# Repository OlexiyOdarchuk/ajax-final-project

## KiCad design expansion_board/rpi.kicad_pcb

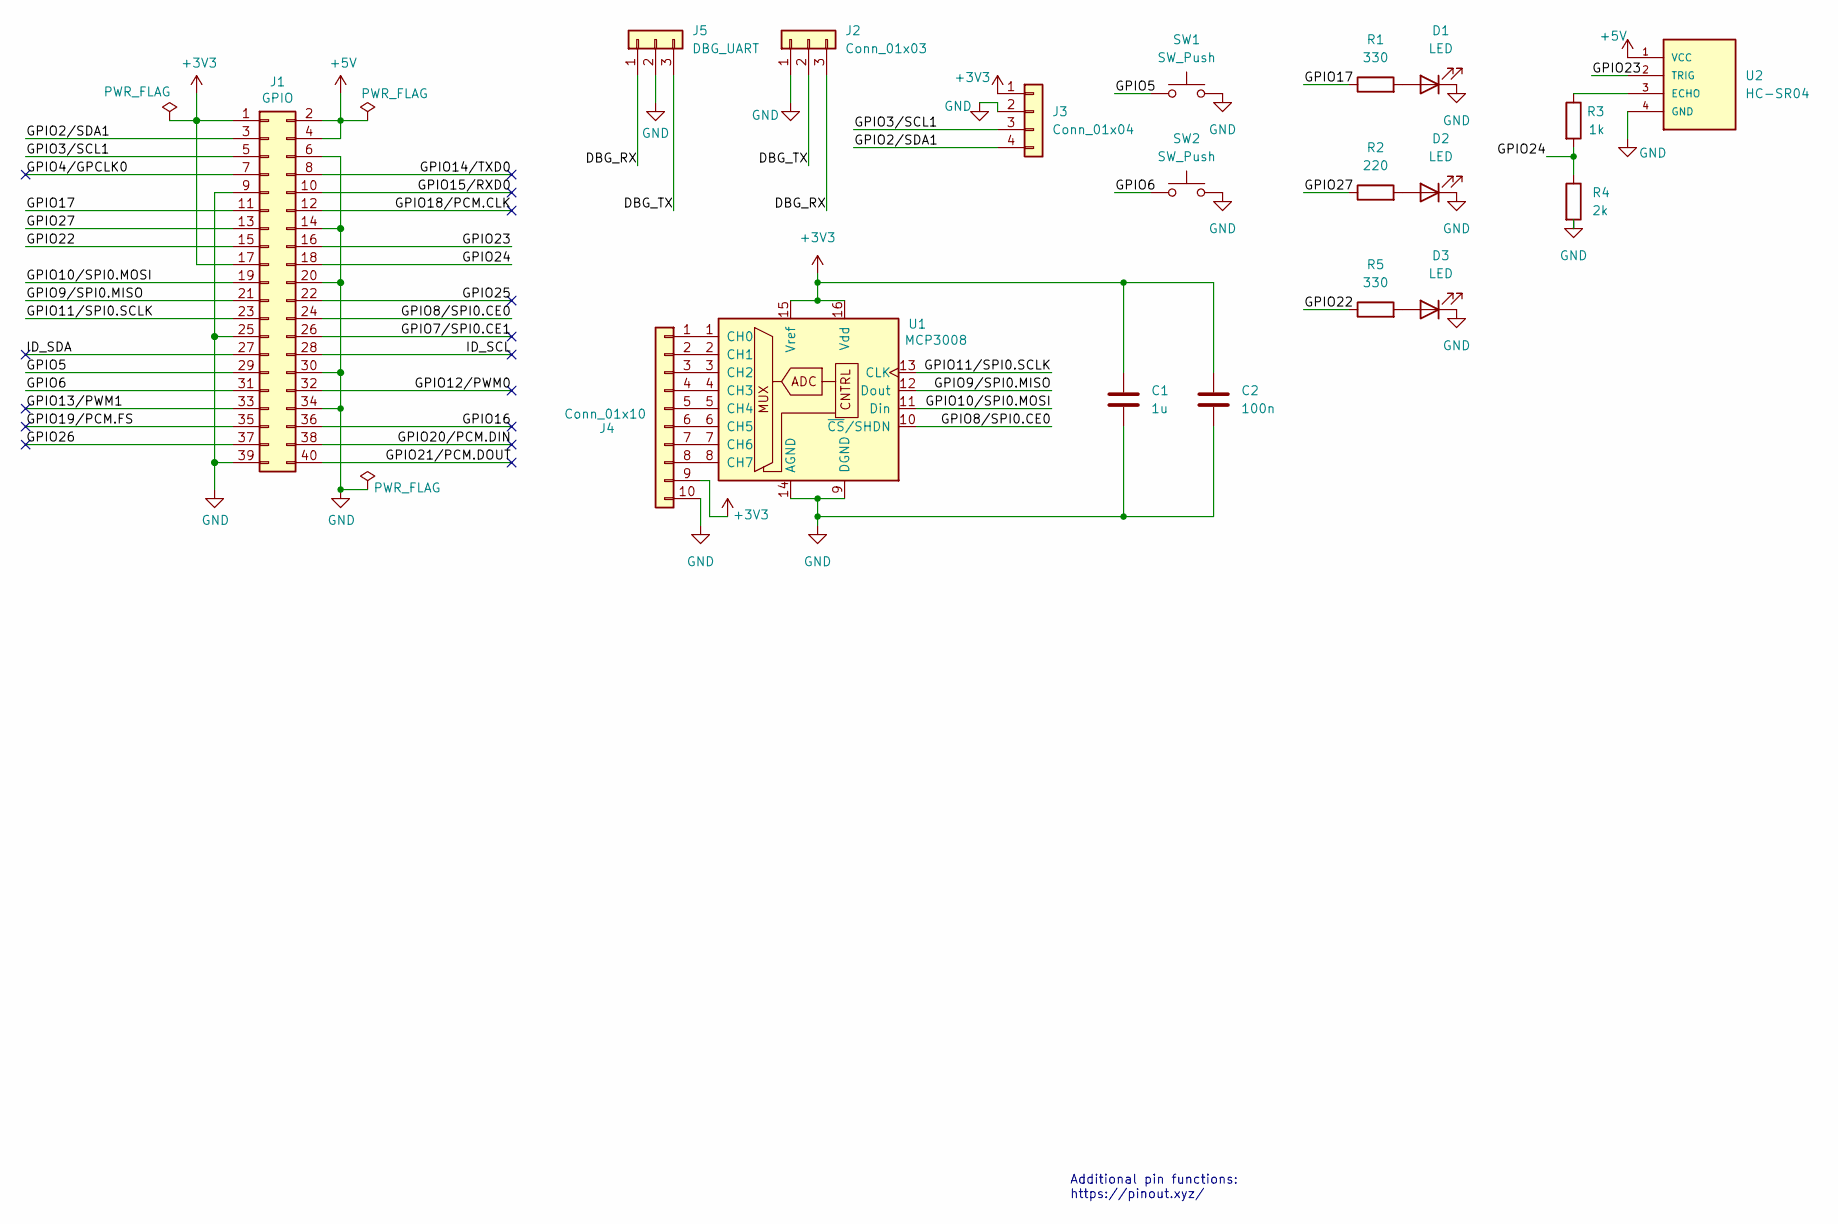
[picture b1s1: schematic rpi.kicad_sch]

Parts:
C1: 1u; C_Disc_D5.0mm_W2.5mm_P5.00mm
C2: 100n; C_Disc_D5.0mm_W2.5mm_P5.00mm
D1, D2, D3: LED; LED_D5.0mm
J1: GPIO; PinSocket_2x20_P2.54mm_Vertical
J2: Conn_01x03; PinHeader_1x03_P2.54mm_Horizontal
J3: Conn_01x04; PinSocket_1x04_P2.54mm_Vertical
J4: Conn_01x10; PinHeader_1x10_P2.54mm_Vertical
J5: DBG_UART; PinHeader_1x03_P2.54mm_Vertical
R1, R5: 330; R_Axial_DIN0207_L6.3mm_D2.5mm_P10.16mm_Horizontal
R2: 220; R_Axial_DIN0207_L6.3mm_D2.5mm_P10.16mm_Horizontal
R3: 1k; R_Axial_DIN0207_L6.3mm_D2.5mm_P10.16mm_Horizontal
R4: 2k; R_Axial_DIN0207_L6.3mm_D2.5mm_P10.16mm_Horizontal
SW1, SW2: SW_Push; SW_PUSH_6mm
U1: MCP3008; DIP-16_W7.62mm
U2: HC-SR04; XCVR_HC-SR04

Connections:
+3V3: C1.1, C2.1, J1.1, J1.17, J3.1, J4.9, U1.15 (Vref), U1.16 (Vdd)
+5V: J1.2, J1.4, U2.1 (VCC)
/DBG_RX: J2.3, J5.1
/DBG_TX: J2.2, J5.3
/GPIO2/SDA1: J1.3, J3.4
/GPIO3/SCL1: J1.5, J3.3
/GPIO4/GPCLK0: J1.7
/GPIO5: J1.29, SW1.1
/GPIO6: J1.31, SW2.1
/GPIO7/SPI0.CE1: J1.26
/GPIO8/SPI0.CE0: J1.24, U1.10 (~CS/SHDN)
/GPIO9/SPI0.MISO: J1.21, U1.12 (Dout)
/GPIO10/SPI0.MOSI: J1.19, U1.11 (Din)
/GPIO11/SPI0.SCLK: J1.23, U1.13 (CLK)
/GPIO12/PWM0: J1.32
/GPIO13/PWM1: J1.33
/GPIO14/TXD0: J1.8
/GPIO15/RXD0: J1.10
/GPIO16: J1.36
/GPIO17: J1.11, R1.1
/GPIO18/PCM.CLK: J1.12
/GPIO19/PCM.FS: J1.35
/GPIO20/PCM.DIN: J1.38
/GPIO21/PCM.DOUT: J1.40
/GPIO22: J1.15, R5.1
/GPIO23: J1.16, U2.2 (TRIG)
/GPIO24: J1.18, R3.2, R4.1
/GPIO25: J1.22
/GPIO26: J1.37
/GPIO27: J1.13, R2.1
/ID_SCL: J1.28
/ID_SDA: J1.27
GND: C1.2, C2.2, D1.1 (K), D2.1 (K), D3.1 (K), J1.6, J1.9, J1.14, J1.20, J1.25, J1.30, J1.34, J1.39, J2.1, J3.2, J4.10, J5.2, R4.2, SW1.2, SW2.2, U1.9 (DGND), U1.14 (AGND), U2.4 (GND)
unnamed: D1.2 (A), R1.2
unnamed: D2.2 (A), R2.2
unnamed: D3.2 (A), R5.2
unnamed: J4.1, U1.1 (CH0)
unnamed: J4.2, U1.2 (CH1)
unnamed: J4.3, U1.3 (CH2)
unnamed: J4.4, U1.4 (CH3)
unnamed: J4.5, U1.5 (CH4)
unnamed: J4.6, U1.6 (CH5)
unnamed: J4.7, U1.7 (CH6)
unnamed: J4.8, U1.8 (CH7)
unnamed: R3.1, U2.3 (ECHO)

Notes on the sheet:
Additional pin functions: https://pinout.xyz/

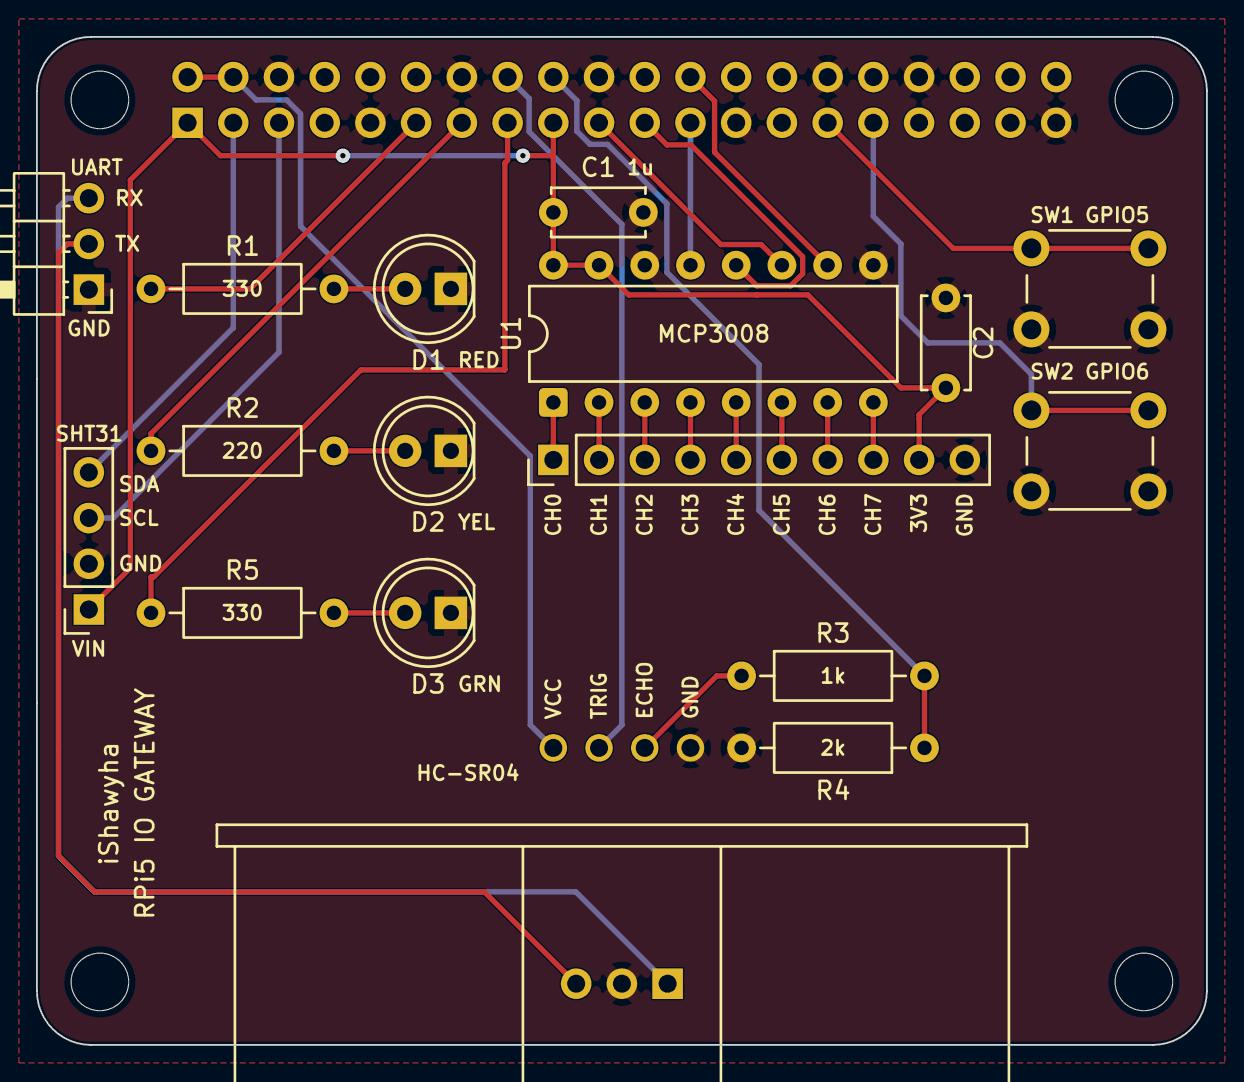
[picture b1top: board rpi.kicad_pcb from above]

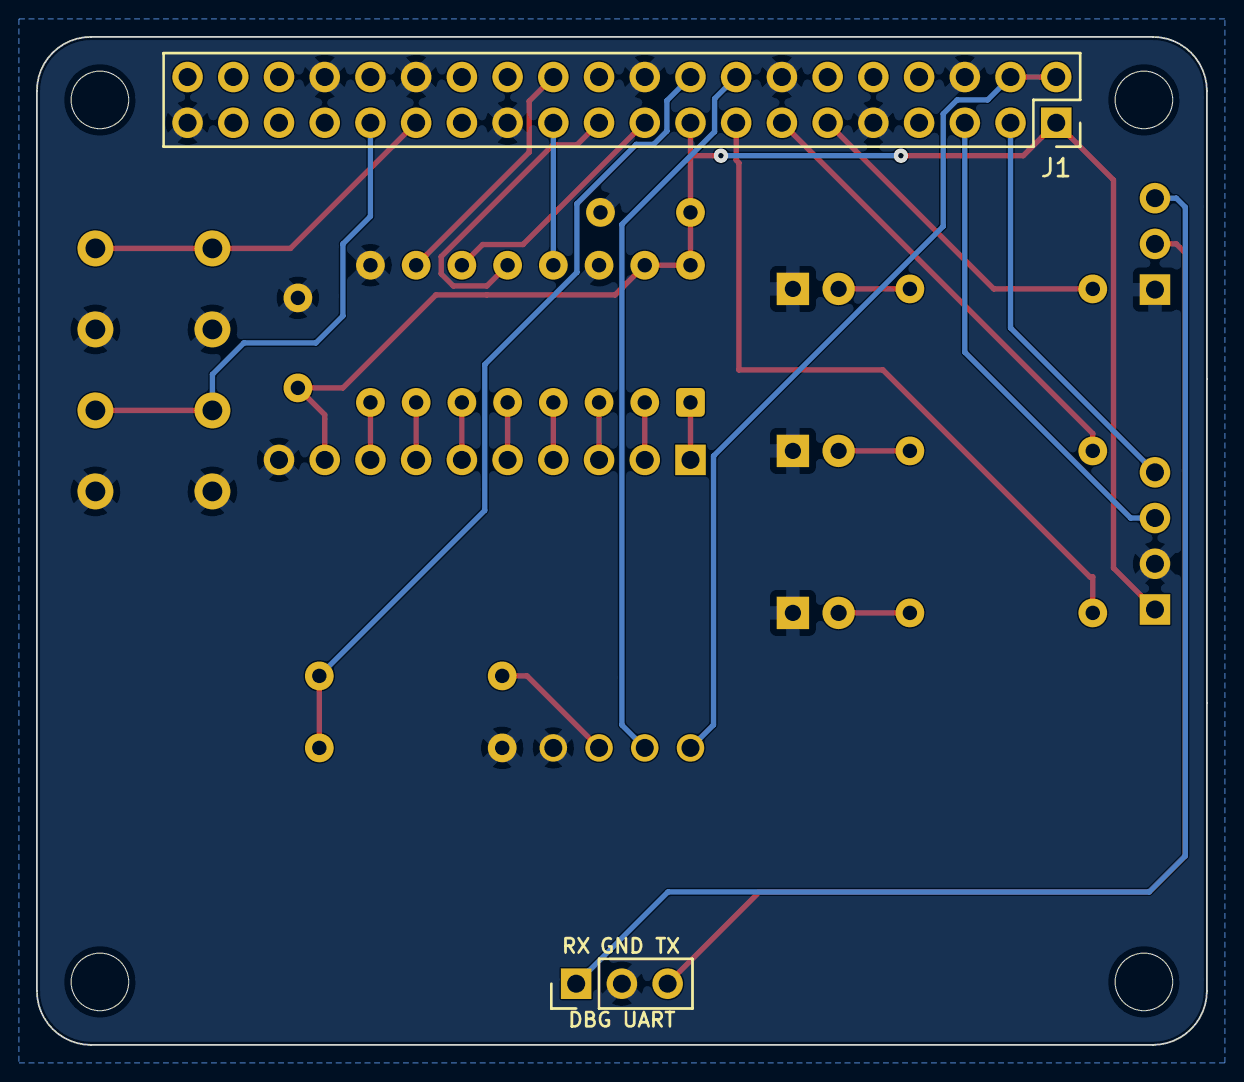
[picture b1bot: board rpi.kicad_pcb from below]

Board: 2 copper layers, 65.0 x 56.0 mm, 23 parts (2 on the bottom side), 30 nets.

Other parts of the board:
MH1, MH2, MH3, MH4: MountingHole_3.2mm
